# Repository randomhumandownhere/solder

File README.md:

# solder
a battery powered cat keychain with blinking LEDs by @randomhumandownhere

## bill of materials:
| Component           | Quantity |
| ------------------- | -------- |
| CR2032 Battery Cell | 1x       |
| 5mm LED             | 2x       |
| 220Ω Resistor       | 2x       |
| 4.7kΩ Resistor      | 2x       |
| 10µF Capacitor      | 2x       |
| 2N3904 Transistor   | 2x       |

## pictures!

the pcb :3

some schematics

my simulation in the falstad circuit simulation applet

final pcb renders!

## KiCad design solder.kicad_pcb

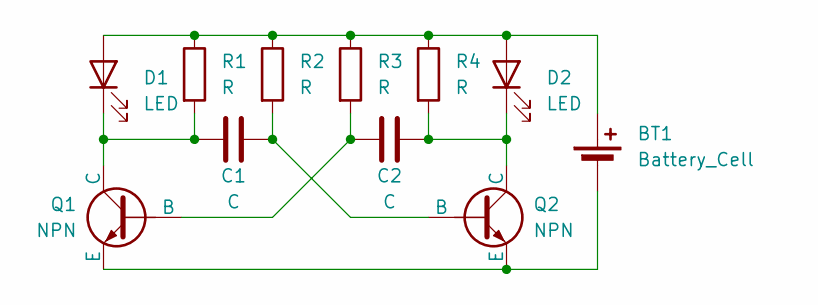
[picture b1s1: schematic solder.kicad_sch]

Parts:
BT1: Battery_Cell; BatteryHolder_Keystone_3034_1x20mm
C1, C2: C; CP_Radial_D8.0mm_P5.00mm
D1, D2: LED; LED_D5.0mm
Q1, Q2: NPN; TO-92L_HandSolder
R1, R2, R3, R4: R; R_Axial_DIN0207_L6.3mm_D2.5mm_P7.62mm_Horizontal

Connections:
unnamed: BT1.1 (+), D1.2 (A), D2.2 (A), R1.1, R2.1, R3.1, R4.1
unnamed: BT1.2 (-), Q1.3 (E), Q2.3 (E)
unnamed: C1.1, D1.1 (K), Q1.1 (C), R1.2
unnamed: C2.2, D2.1 (K), Q2.1 (C), R4.2
unnamed: C2.1, Q1.2 (B), R3.2
unnamed: C1.2, Q2.2 (B), R2.2

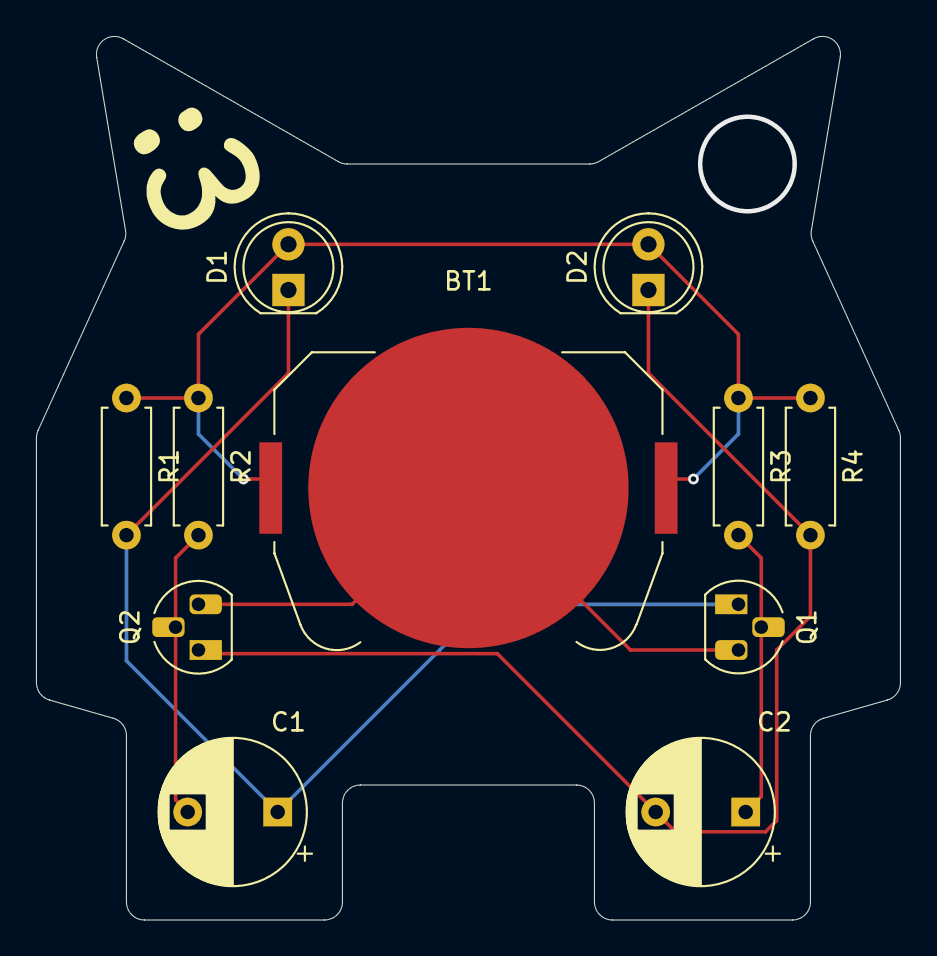
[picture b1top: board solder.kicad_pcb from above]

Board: 2 copper layers, 48.0 x 49.1 mm, 11 parts (0 on the bottom side), 6 nets.

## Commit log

2025-06-28 its soldering time!
2025-06-28 update!!! made LEDs blink
2025-06-29 added pcb traces and back silkscreen
